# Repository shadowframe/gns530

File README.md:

# GNS 530

GNS 530 MSFS - Mobiflight - Gerber PCB - 3D Model Files and PARTLIST

# KiCad / PCB

Sourcefiles for the PCB´s are KiCad Files. 
The Blueprints, 3D-Files and Symbols from my libary are located at the "KiCad_Parts" Folder.

# Parts

## Connectors

There two options for the connection from the pcb to the arduino

### 1. Option, Solid Cable and Plug ...

[STRAIGHT TYPE Header Pin Plug](https://de.aliexpress.com/item/1005007846925877.html?spm=a2g0o.productlist.main.55.5abcerOMerOMje&algo_pvid=66fb1220-13a7-4d9d-a78b-482d9e5e1eb2&aem_p4p_detail=202410261159314868643083656000000421741&algo_exp_id=66fb1220-13a7-4d9d-a78b-482d9e5e1eb2-27&pdp_npi=4%40dis%21EUR%211.69%211.69%21%21%2112.74%2112.74%21%402103868a17299691711727939e9216%2112000042511077902%21sea%21DE%21104089574%21X&curPageLogUid=Y6gYAISRx9tU&utparam-url=scene%3Asearch%7Cquery_from%3A&search_p4p_id=202410261159314868643083656000000421741_8)

[Ribbon Cable](https://de.aliexpress.com/item/1005005859783880.html?spm=a2g0o.detail.pcDetailTopMoreOtherSeller.1.2486CrSQCrSQqQ&gps-id=pcDetailTopMoreOtherSeller&scm=1007.40000.327270.0&scm_id=1007.40000.327270.0&scm-url=1007.40000.327270.0&pvid=a72eb635-beef-4724-aee7-2530dc39570b&_t=gps-id:pcDetailTopMoreOtherSeller,scm-url:1007.40000.327270.0,pvid:a72eb635-beef-4724-aee7-2530dc39570b,tpp_buckets:668%232846%238112%231997&pdp_npi=4%40dis%21EUR%210.87%210.80%21%21%210.92%210.85%21%40211b80d117299692154805139e87a7%2112000034603686094%21rec%21DE%21104089574%21XZ&utparam-url=scene%3ApcDetailTopMoreOtherSeller%7Cquery_from%3A&search_p4p_id=202410261200155281471350134661242704_0#nav-specification)

### 2. Option, PIN Header and DuPont Cable (Breakboard Style) ...

[Du Pont Cable](https://de.aliexpress.com/item/1005005501503609.html?spm=a2g0o.order_list.order_list_main.5.18a45c5fjZwXdy&gatewayAdapt=glo2deu)

[Header PIN](https://de.aliexpress.com/item/4000988113226.html?spm=a2g0o.productlist.main.1.67e72ff4d7ew5Z&algo_pvid=24823ea3-8e49-4015-b8c3-e4b003e2bb26&algo_exp_id=24823ea3-8e49-4015-b8c3-e4b003e2bb26-0&pdp_npi=4%40dis%21EUR%211.29%211.29%21%21%211.36%211.36%21%40211b813f17299745090976722eace9%2110000013202368848%21sea%21DE%21104089574%21X&curPageLogUid=gu0EKOwNoz6Y&utparam-url=scene%3Asearch%7Cquery_from%3A)

## Encoder

[EC11EBB24C03 DUAL ENCODER](https://de.aliexpress.com/item/1005004143502259.html?spm=a2g0o.order_list.order_list_main.17.13e85c5fBGPmSf&gatewayAdapt=glo2deu)

EC11E1534408 or EC11E15244G1

[EC11E15244G1](https://componentsearchengine.com/part-view/EC11E15244G1/ALPS%20Electric)

[EC11E1534408](https://componentsearchengine.com/part-view/EC11E1534408/ALPS%20Electric)

## Microcontroller

Arduino Mega 2560

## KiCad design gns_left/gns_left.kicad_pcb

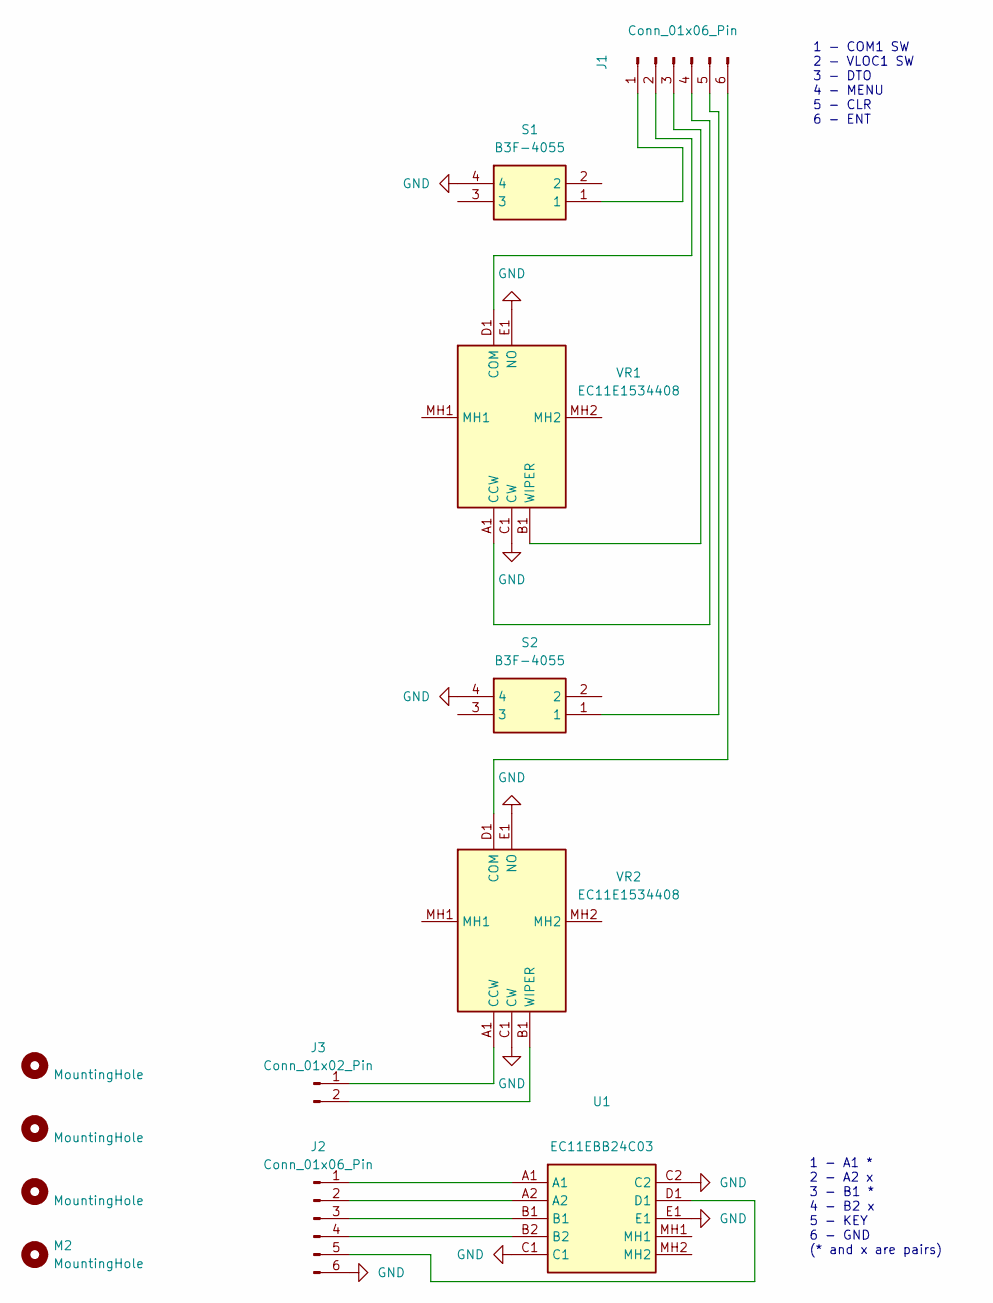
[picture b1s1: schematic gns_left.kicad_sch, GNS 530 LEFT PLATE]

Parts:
H2, H3, H4: MountingHole; MountingHole_2.2mm_M2
J1, J2: Conn_01x06_Pin; PinSocket_1x06_P2.00mm_Vertical
J3: Conn_01x02_Pin; PinHeader_1x02_P2.00mm_Vertical
M2: MountingHole; MountingHole_2.2mm_M2
S1, S2: B3F-4055; Omron-B3F-4055-switch; Manufacturer_Part_Number B3F-4055; Mouser Part Number 653-B3F-4055
U1: EC11EBB24C03; Manufacturer_Part_Number EC11EBB24C03; Mouser Part Number 688-EC11EBB24C03
VR1, VR2: EC11E1534408; Manufacturer_Part_Number EC11E1534408; Mouser Part Number 688-EC11E1534408

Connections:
GND: J2.6, S1.4, S2.4, U1.C1, U1.C2, U1.E1, VR1.C1 (CW), VR1.E1 (NO), VR2.C1 (CW), VR2.E1 (NO)
unnamed: J1.1, S1.1
unnamed: J1.2, VR1.D1 (COM)
unnamed: J1.3, VR1.B1 (WIPER)
unnamed: J1.4, VR1.A1 (CCW)
unnamed: J1.5, S2.1
unnamed: J1.6, VR2.D1 (COM)
unnamed: J2.1, U1.A1
unnamed: J2.2, U1.A2
unnamed: J2.3, U1.B1
unnamed: J2.4, U1.B2
unnamed: J2.5, U1.D1
unnamed: J3.1, VR2.A1 (CCW)
unnamed: J3.2, VR2.B1 (WIPER)

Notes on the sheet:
1 - A1 * 2 - A2 x 3 - B1 * 4 - B2 x 5 - KEY 6 - GND (* and x are pairs)
1 - COM1 SW 2 - VLOC1 SW 3 - DTO 4 - MENU 5 - CLR 6 - ENT

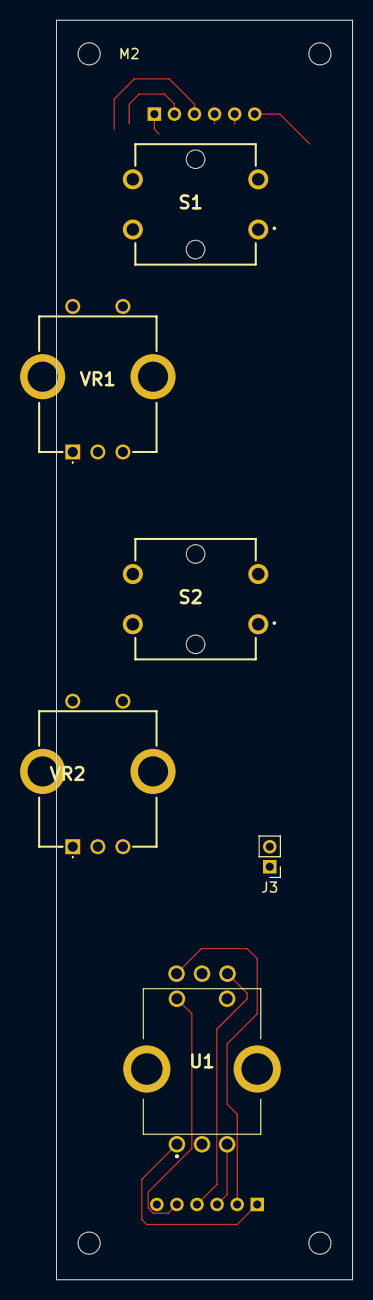
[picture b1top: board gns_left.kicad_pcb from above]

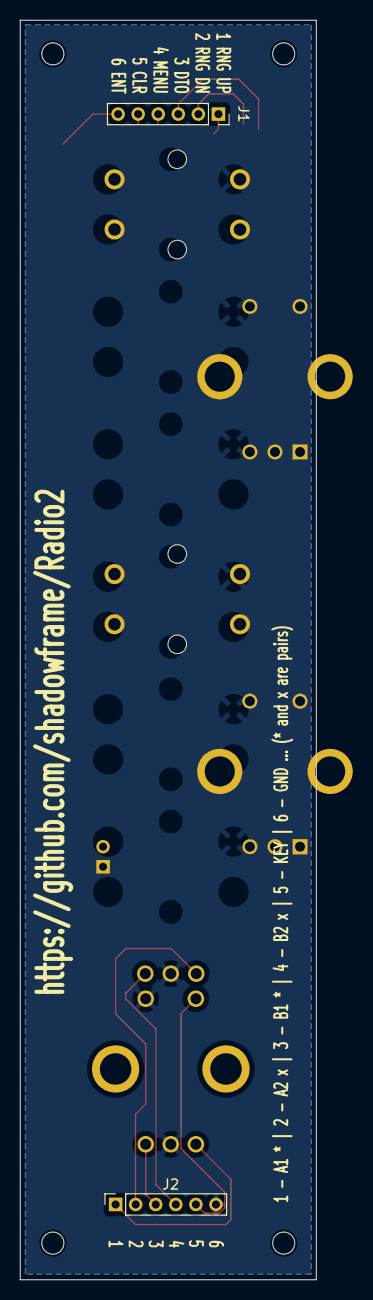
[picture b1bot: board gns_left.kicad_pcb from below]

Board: 4 copper layers, 29.5 x 125.5 mm, 12 parts (2 on the bottom side), 14 nets.

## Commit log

2024-10-26 left_start
2024-10-26 nothing ...
2024-10-26 kicad elements
2024-10-26 docs
2024-10-27 readme
